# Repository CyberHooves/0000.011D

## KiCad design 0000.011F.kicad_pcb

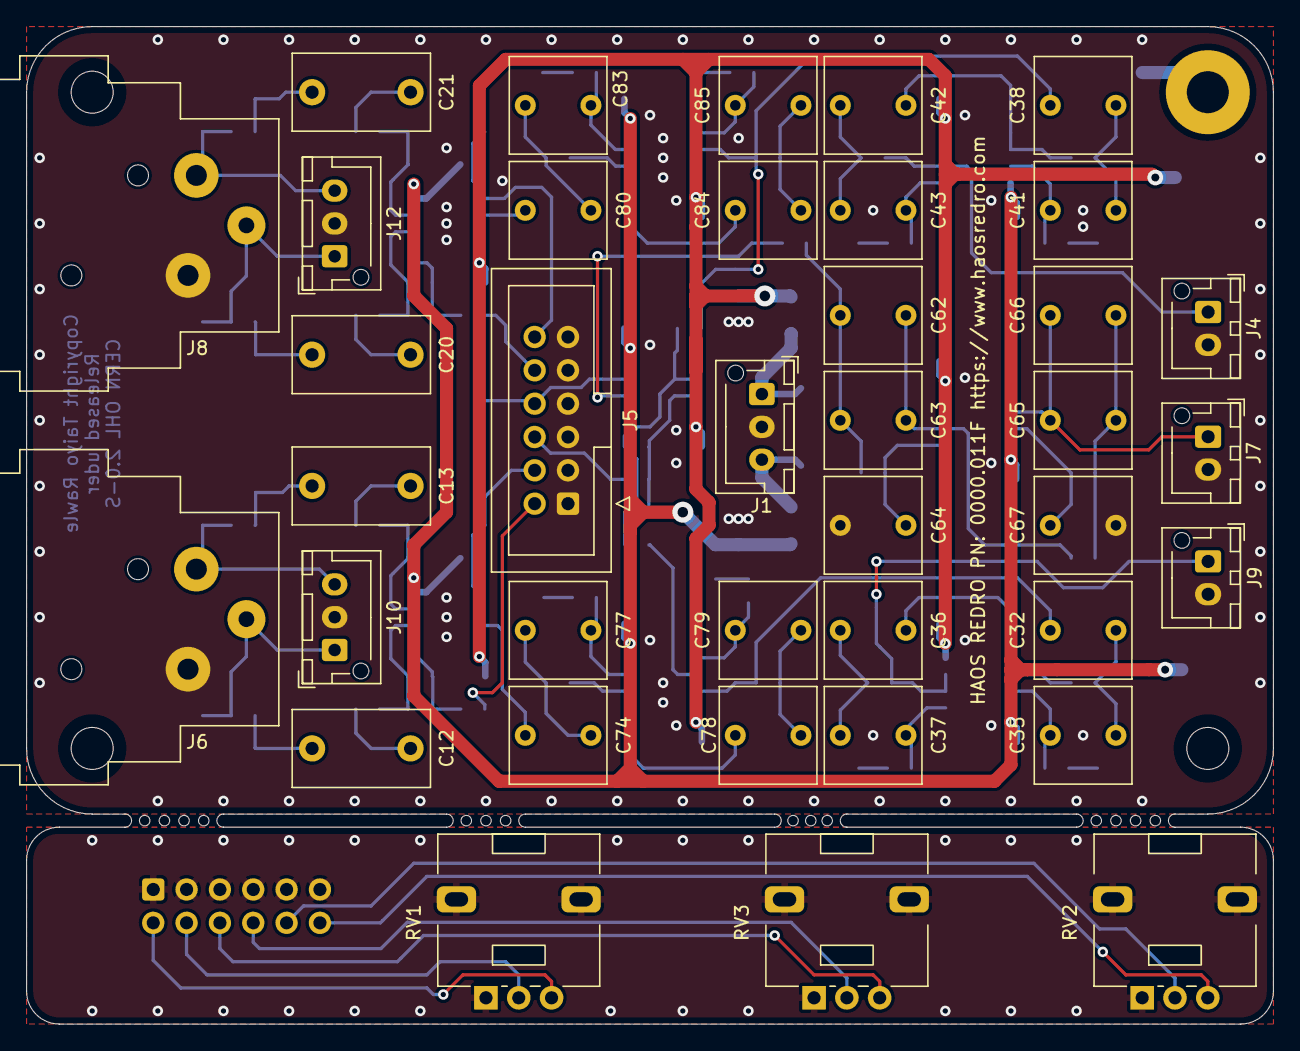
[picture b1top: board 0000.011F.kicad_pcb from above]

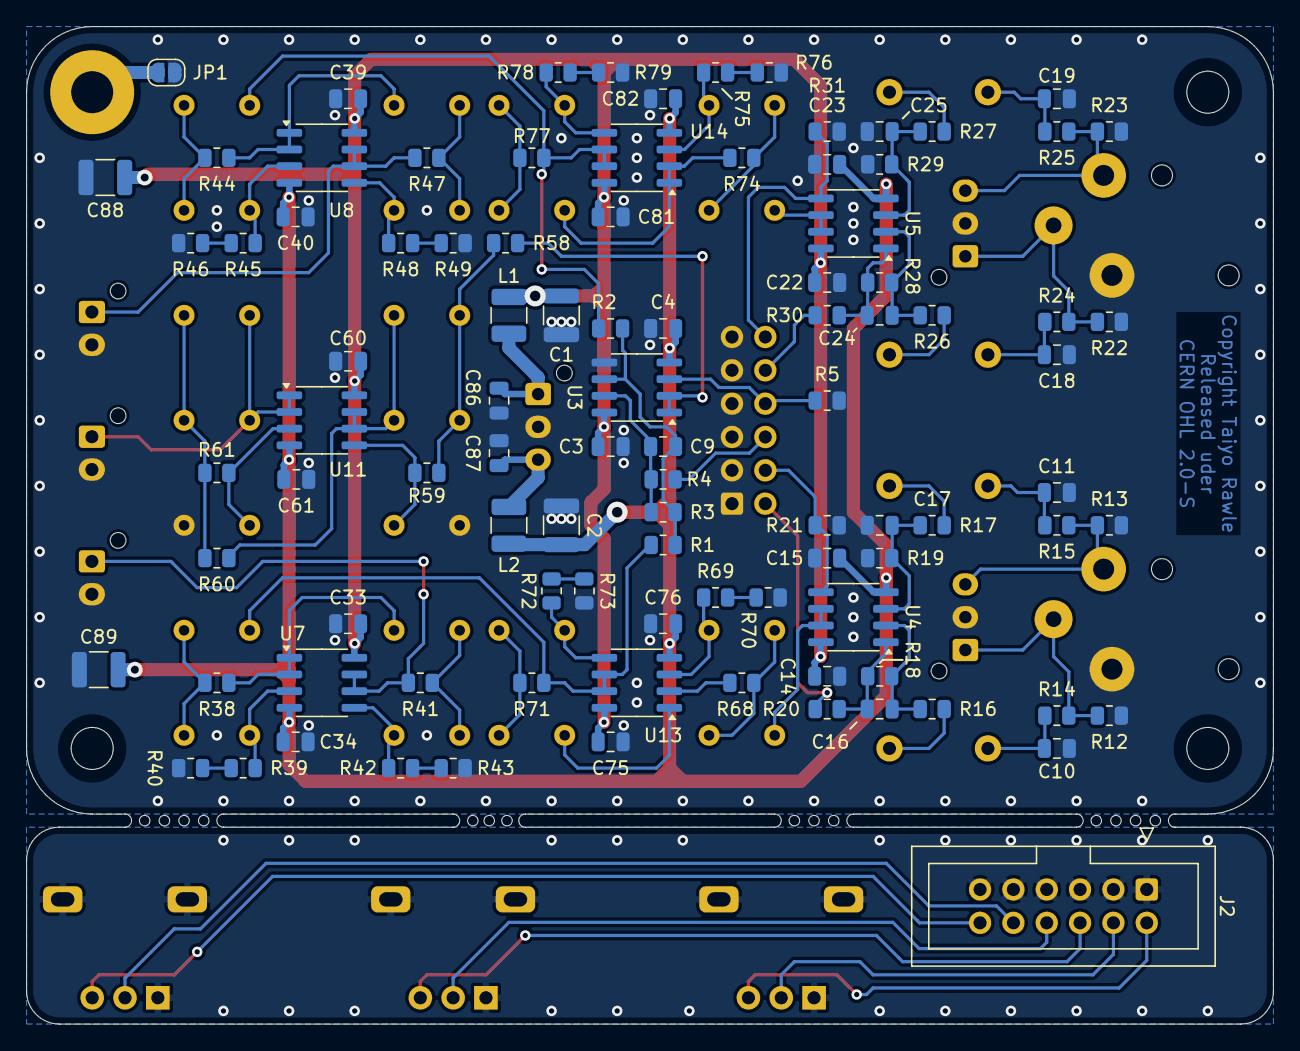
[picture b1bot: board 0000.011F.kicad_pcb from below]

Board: 2 copper layers, 95.0 x 76.0 mm, 152 parts (96 on the bottom side), 80 nets.

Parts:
C1, C2, C88, C89: 106; C_1210_3225Metric
C3, C4, C14, C15, C22, C23, C33, C34, C39, C40, C60, C61, C75, C76, C81, C82, C86, C87: 104; C_0805_2012Metric
C9, C10, C11, C16, C17, C18, C19, C24, C25: 221; C_0805_2012Metric
C12, C13, C20, C21: 225; C_Rect_L10.3mm_W5.7mm_P7.50mm_MKS4
C32, C35, C36, C37, C38, C41, C42, C43, C62, C63, C64, C65, C66, C67, C74, C77, C78, C79, C80, C83, C84, C85: C; C_Rect_L7.2mm_W7.2mm_P5.00mm_FKS2_FKP2_MKS2_MKP2
H1, H2, H3: M3; MountingHole_3.2mm_M3
H4: M3; MountingHole_3.2mm_M3_Pad
H5, H6, H7, H8, H9, H10, H11, H12, H13, H14, H15, H16, H17, H18: 0.8; HOLE_0.8
J1, J10, J12: XH; JST_XH_B3B-XH-AM_1x03_P2.50mm_Vertical
J2, J5: BH254; IDC-Header_2x06_P2.54mm_Vertical
J4, J7, J9: XH; JST_XH_B2B-XH-AM_1x02_P2.50mm_Vertical
J6, J8: NC3FAH1; Jack_XLR_Neutrik_NC3FAH1_Horizontal
JP1: blob; SolderJumper-2_P1.3mm_Open_RoundedPad1.0x1.5mm
L1, L2: 22; L_1210_3225Metric
R1, R2: 20K; R_0805_2012Metric
R3, R16, R17, R18, R19, R26, R27, R28, R29: 10K; R_0805_2012Metric
R4, R14, R15, R20, R24, R25, R30: 100; R_0805_2012Metric
R5, R21, R31: 5K6; R_0805_2012Metric
R12, R13, R22, R23: 1M; R_0805_2012Metric
R38, R39, R40, R41, R42, R43, R44, R45, R46, R47, R48, R49, R58, R59, R60, R61, R68, R69, R70, R71, R72, R73, R74, R75, R76, R77, R78, R79: R; R_0805_2012Metric
RV1, RV2, RV3: RK09L1140A2U; Potentiometer_Alps_RK09L_Single_Vertical
U3, U4, U5, U7, U8, U11, U13, U14: TL072; SOIC-8_3.9x4.9mm_P1.27mm

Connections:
+15V: C1.1, C3.1, C14.1, C22.1, C33.1, C39.1, C60.1, C75.1, C81.1, C88.1, L1.2, U3.8 (V+), U4.8 (V+), U5.8 (V+), U7.8 (V+), U8.8 (V+), U11.8 (V+), U13.8 (V+), U14.8 (V+)
-15V: C2.2, C4.2, C15.2, C23.2, C34.2, C40.2, C61.2, C76.2, C82.2, C89.2, L2.2, U3.4 (V-), U4.4 (V-), U5.4 (V-), U7.4 (V-), U8.4 (V-), U11.4 (V-), U13.4 (V-), U14.4 (V-)
/Input stage CH1/OUT: C74.1, U4.6 (-), U4.7
/Input stage CH1/POTH: J5.2, R20.2
/Input stage CH1/POTW: J5.4, R21.2, U4.5 (+)
/Input stage CH2/OUT: C80.1, U5.6 (-), U5.7
/Input stage CH2/POTH: J5.10, R30.2
/Input stage CH2/POTW: J5.12, R31.2, U5.5 (+)
/SPH: J5.6, R4.2
/SPW: J5.8, R5.2, U3.3 (+)
/Sub highpass CH1/IN: C32.1, R1.1, R71.2, U13.6 (-), U13.7
/Sub highpass CH1/OUT: J9.1, R41.2, U7.6 (-), U7.7
/Sub highpass CH2/IN: C38.1, R2.1, R77.2, U14.6 (-), U14.7
/Sub highpass CH2/OUT: J4.1, R47.2, U8.6 (-), U8.7
/Sub lowpass1/IN: R58.1, U3.1, U3.2 (-)
/Sub lowpass1/OUT: C65.1, C66.1, J7.1, U11.1, U11.2 (-)
GND: C1.2, C2.1, C3.2, C4.1, C10.2, C11.1, C14.2, C15.1, C17.2, C18.2, C19.1, C22.2, C23.1, C25.2, C33.2, C34.1, C39.2, C40.1, C60.2, C61.1, C64.2, C67.2, C75.2, C76.1, C81.2, C82.1, C86.2, C87.1, C88.2, C89.1, J1.2, J4.2, J5.1, J5.3, J5.5, J5.7, J5.9, J5.11, J6.1, J7.2, J8.1, J9.2, J10.2, J12.2, JP1.1 (A), R5.1, R12.1, R13.2, R19.2, R21.1, R22.1, R23.2, R29.2, R31.1, R40.1, R43.1, R46.1, R49.1, R70.1, R73.1, R76.1, R79.1, U3.5 (+)
unnamed: C9.2, R3.2, R4.1, U3.7
unnamed: C10.1, C12.1, R14.2
unnamed: C11.2, C13.1, R15.2
unnamed: C12.2, R16.1
unnamed: C13.2, R17.1
unnamed: C16.2, R18.2, R20.1, U4.1
unnamed: C18.1, C20.1, R24.2
unnamed: C19.2, C21.1, R25.2
unnamed: C20.2, R26.1
unnamed: C21.2, R27.1
unnamed: C24.2, R28.2, R30.1, U5.1
unnamed: C32.2, C35.1, R38.1
unnamed: C36.2, C37.1, R41.1
unnamed: C38.2, C41.1, R44.1
unnamed: C42.2, C43.1, R47.1
unnamed: C62.2, C63.2, R58.2, R59.1
unnamed: C65.2, C66.2, R60.2, R61.1
unnamed: C74.2, C77.1, R68.1
unnamed: C78.2, C79.1, R71.1
unnamed: C80.2, C83.1, R74.1
unnamed: C84.2, C85.1, R77.1
unnamed: C86.1, J1.1, L1.1
unnamed: C87.2, J1.3, L2.1
unnamed: J2.1, J2.3, J2.5, J2.7, J2.9, J2.11, RV1.1, RV1.MP (MountPin), RV2.1, RV2.MP (MountPin), RV3.1, RV3.MP (MountPin)
unnamed: J2.2, RV1.3
unnamed: J2.4, RV1.2
unnamed: J2.6, RV3.3
unnamed: J2.8, RV3.2
unnamed: J2.10, RV2.2
unnamed: J2.12, RV2.3
unnamed: J6.3, J10.1, R12.2, R14.1
unnamed: J6.2, J10.3, R13.1, R15.1
unnamed: J8.3, J12.1, R22.2, R24.1
unnamed: J8.2, J12.3, R23.1, R25.1
unnamed: H4.1, JP1.2 (B)
unnamed: R39.1, R40.2
unnamed: R42.1, R43.2
unnamed: R45.1, R46.2
unnamed: R48.1, R49.2
unnamed: R69.1, R70.2
unnamed: R72.1, R73.2
unnamed: R75.1, R76.2
unnamed: R78.1, R79.2
unnamed: C9.1, R1.2, R2.2, R3.1, U3.6 (-)
unnamed: C17.1, R17.2, R19.1, U4.3 (+)
unnamed: C16.1, R16.2, R18.1, U4.2 (-)
unnamed: C25.1, R27.2, R29.1, U5.3 (+)
unnamed: C24.1, R26.2, R28.1, U5.2 (-)
unnamed: C35.2, R39.2, U7.3 (+)
unnamed: C36.1, R38.2, U7.1, U7.2 (-)
unnamed: C37.2, R42.2, U7.5 (+)
unnamed: C41.2, R45.2, U8.3 (+)
unnamed: C42.1, R44.2, U8.1, U8.2 (-)
unnamed: C43.2, R48.2, U8.5 (+)
unnamed: C67.1, R61.2, U11.3 (+)
unnamed: C64.1, R59.2, U11.5 (+)
unnamed: C62.1, C63.1, R60.1, U11.6 (-), U11.7
unnamed: C77.2, R69.2, U13.3 (+)
unnamed: C78.1, R68.2, U13.1, U13.2 (-)
unnamed: C79.2, R72.2, U13.5 (+)
unnamed: C83.2, R75.2, U14.3 (+)
unnamed: C84.1, R74.2, U14.1, U14.2 (-)
unnamed: C85.2, R78.2, U14.5 (+)

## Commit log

2025-06-06 Added XLR input connectors for direct panel mounting. Added snap-off board for the level control pots with ribbon cable connection to the main board.

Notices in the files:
0000.011F.kicad_pcb:
Copyright Taiyo Rawle 2025
Released under CERN OHL 2.0-S
CERN OHL 2.0-S
